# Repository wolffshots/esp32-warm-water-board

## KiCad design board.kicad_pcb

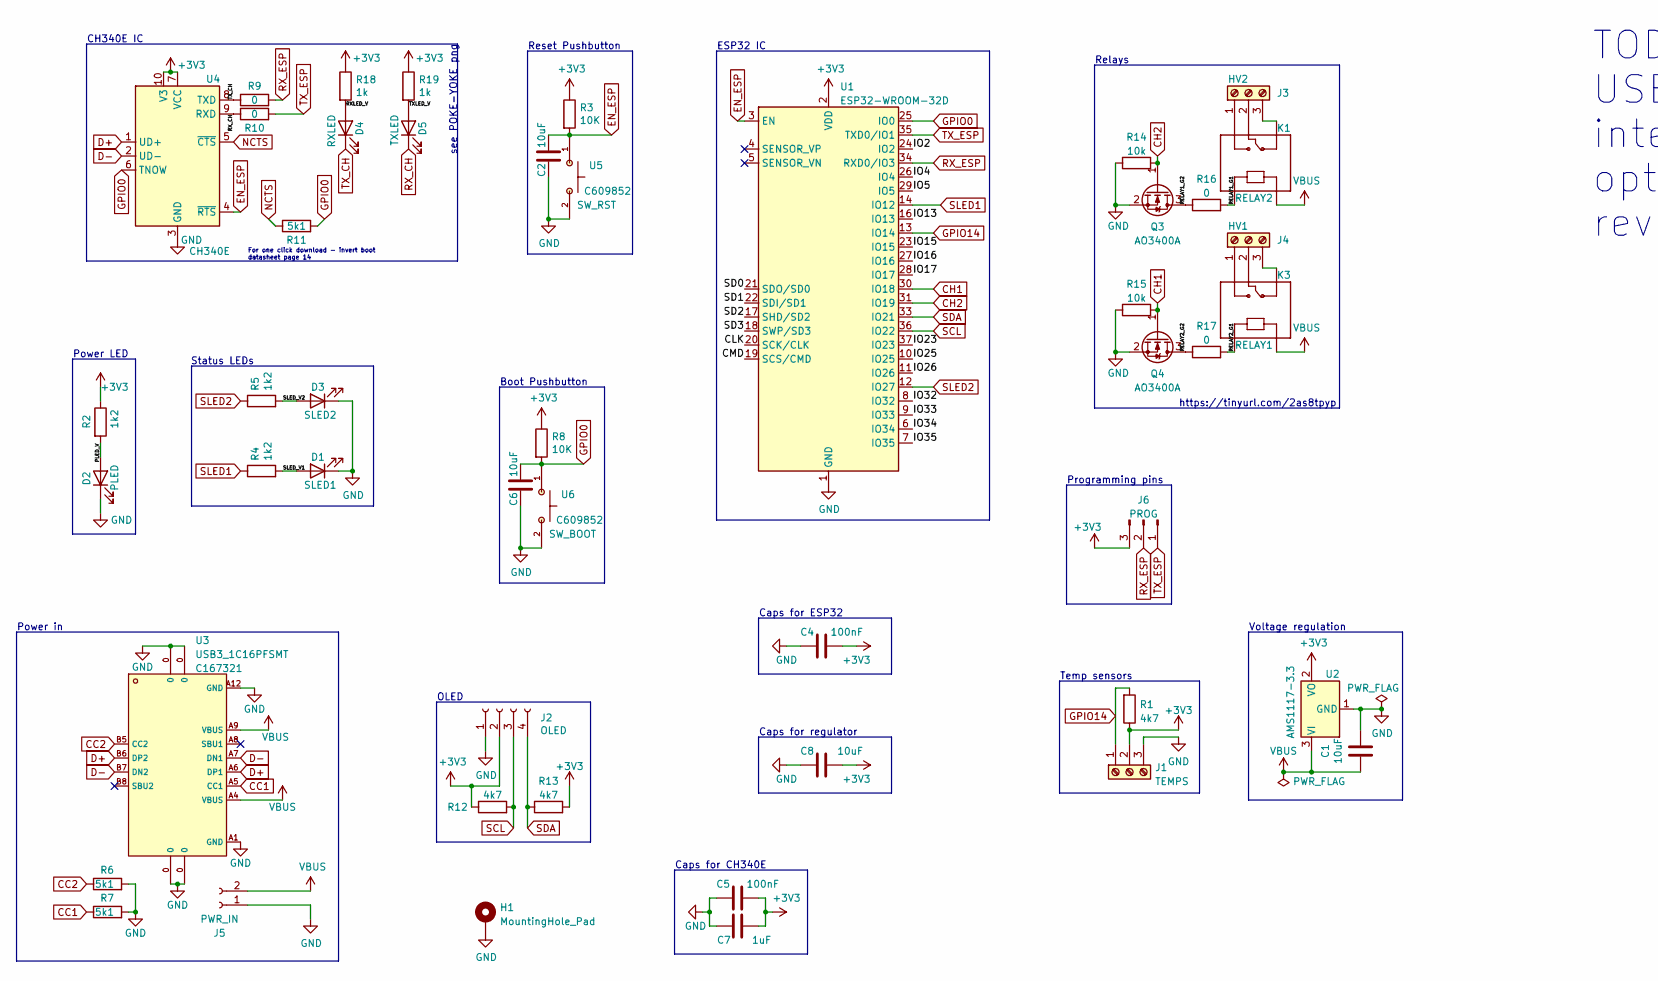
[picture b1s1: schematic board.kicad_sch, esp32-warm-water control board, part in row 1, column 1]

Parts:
C1, C2, C6: 10uF; C_0402_1005Metric; Part No C15850; LCSC C15850
C4, C5: 100nF; C_0402_1005Metric; Part No C49678; LCSC C49678
C7: 1uF; C_0402_1005Metric; Part No C15850; LCSC C15850
C8: 10uF; C_0402_1005Metric; Part No C49678; LCSC C49678
D1: SLED1; LED_0603_1608Metric; Part No C2286; LCSC C2286
D2: PLED; LED_0603_1608Metric; Part No C2286; LCSC C2286
D3: SLED2; LED_0603_1608Metric; Part No C2286; LCSC C2286
D4: RXLED; LED_0603_1608Metric; Part No C2286; LCSC C2286
D5: TXLED; LED_0603_1608Metric; Part No C2286; LCSC C2286
H1: MountingHole_Pad; MountingHole_2.2mm_M2_DIN965_Pad
J1: TEMPS; TerminalBlock_Phoenix_PT-1,5-3-5.0-H_1x03_P5.00mm_Horizontal
J2: OLED; PinSocket_1x04_P2.54mm_Vertical
J3: HV2; TerminalBlock_Phoenix_PT-1,5-3-5.0-H_1x03_P5.00mm_Horizontal
J4: HV1; TerminalBlock_Phoenix_PT-1,5-3-5.0-H_1x03_P5.00mm_Horizontal
J5: PWR_IN; PinHeader_2x01_P2.54mm_Vertical
J6: PROG; PinHeader_1x03_P2.54mm_Vertical
K1: RELAY2; RELAY_SRD-05VDC-SL-C
K3: RELAY1; RELAY_SRD-05VDC-SL-C
Q3, Q4: AO3400A; SOT-23
R1: 4k7; R_0402_1005Metric; Part No C17673; LCSC C17673
R2, R4, R5: 1k2; R_0402_1005Metric; Part No C17630; LCSC C17630
R3, R8: 10K; R_0402_1005Metric; Part No C17414; LCSC C17414
R6, R7, R11: 5k1; R_0402_1005Metric
R9, R10, R16, R17: 0; R_0402_1005Metric
R12, R13: 4k7; R_0402_1005Metric
R14, R15: 10k; R_0402_1005Metric
R18, R19: 1k; R_0402_1005Metric; Part No C17630; LCSC C17630
U1: ESP32-WROOM-32D; ESP32-WROOM-32
U2: AMS1117-3.3; SOT-223-3_TabPin2; Part No C6186; LCSC C6186
U3: USB3_1C16PFSMT; USB-C-SMD_TYPE-C-USB-17; LCSC C167321
U4: CH340E; MSOP-10_3x3mm_P0.5mm
U5: SW_RST; SW-SMD_L6.0-W3.5-LS8.0; LCSC C609852
U6: SW_BOOT; SW-SMD_L6.0-W3.5-LS8.0; LCSC C609852

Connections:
+3V3: C4.2, C5.2, C7.1, C8.2, J1.2, J2.2, J6.3, R1.1, R2.1, R3.1, R8.1, R12.1, R13.2, R18.1, R19.1, U1.2 (VDD), U2.2 (VO), U4.7 (VCC), U4.10 (V3)
/CLK: U1.20 (SCK/CLK)
/CMD: U1.19 (SCS/CMD)
/IO2: U1.24 (IO2)
/IO4: U1.26 (IO4)
/IO5: U1.29 (IO5)
/IO13: U1.16 (IO13)
/IO15: U1.23 (IO15)
/IO16: U1.27 (IO16)
/IO17: U1.28 (IO17)
/IO23: U1.37 (IO23)
/IO25: U1.10 (IO25)
/IO26: U1.11 (IO26)
/IO32: U1.8 (IO32)
/IO33: U1.9 (IO33)
/IO34: U1.6 (IO34)
/IO35: U1.7 (IO35)
/PLED_V: D2.2 (A), R2.2
/RELAY1_G1: K1.A1, R16.2
/RELAY1_G2: Q3.3 (D), R16.1
/RELAY2_G1: K3.A1, R17.2
/RELAY2_G2: Q4.3 (D), R17.1
/RXLED_V: D4.2 (A), R18.2
/SD0: U1.21 (SDO/SD0)
/SD1: U1.22 (SDI/SD1)
/SD2: U1.17 (SHD/SD2)
/SD3: U1.18 (SWP/SD3)
/SLED_V1: D1.2 (A), R4.2
/SLED_V2: D3.2 (A), R5.2
/TXLED_V: D5.2 (A), R19.2
CC1: R7.1, U3.A5 (CC1)
CC2: R6.1, U3.B5 (CC2)
CH1: Q4.1 (G), R15.2, U1.30 (IO18)
CH2: Q3.1 (G), R14.2, U1.31 (IO19)
D+: U3.A6 (DP1), U3.B6 (DP2), U4.1 (UD+)
D-: U3.A7 (DN1), U3.B7 (DN2), U4.2 (UD-)
EN_ESP: C2.2, R3.2, U1.3 (EN), U4.4 (~RTS), U5.1
GND: C1.1, C2.1, C4.1, C5.1, C6.1, C7.2, C8.1, D1.1 (K), D2.1 (K), D3.1 (K), H1.1, J1.3, J2.1, J5.1, Q3.2 (S), Q4.2 (S), R6.2, R7.2, R14.1, R15.1, U1.1 (GND), U1.15 (GND), U1.38 (GND), U1.39 (GND), U2.1 (GND), U3.0, U3.A1 (GND), U3.A12 (GND), U4.3 (GND), U5.2, U6.2
GPIO0: C6.2, R8.2, R11.2, U1.25 (IO0), U4.6 (TNOW), U6.1
GPIO14: J1.1, R1.2, U1.13 (IO14)
NCTS: R11.1, U4.5 (~CTS)
unnamed: J3.1, K1.NO
unnamed: J3.2, K1.COM
unnamed: J3.3, K1.NC
unnamed: J4.1, K3.NO
unnamed: J4.2, K3.COM
unnamed: J4.3, K3.NC
RX_CH: D5.1 (K), R10.1, U4.9 (RXD)
RX_ESP: J6.2, R9.2, U1.34 (RXD0/IO3)
SCL: J2.3, R12.2, U1.36 (IO22)
SDA: J2.4, R13.1, U1.33 (IO21)
SLED1: R4.1, U1.14 (IO12)
SLED2: R5.1, U1.12 (IO27)
TX_CH: D4.1 (K), R9.1, U4.8 (TXD)
TX_ESP: J6.1, R10.2, U1.35 (TXD0/IO1)
VBUS: C1.2, J5.2, K1.A2, K3.A2, U2.3 (VI), U3.A4 (VBUS), U3.A9 (VBUS)

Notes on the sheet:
TODO: USB footprint integrate relay (https://www.robotics.org.za/SRD-5VDC-SL-C) opto isolator EL3H7(B)(TA)-G review Schaltplan
Reset Pushbutton
CH340E IC
For one click download - invert boot datasheet page 14
Caps for ESP32
Voltage regulation
Power LED
Relays
Caps for regulator
Programming pins
https://tinyurl.com/2as8tpyp
ESP32 IC
OLED
Caps for CH340E
Status LEDs
Temp sensors
Power in
see POKE-YOKE png
Boot Pushbutton

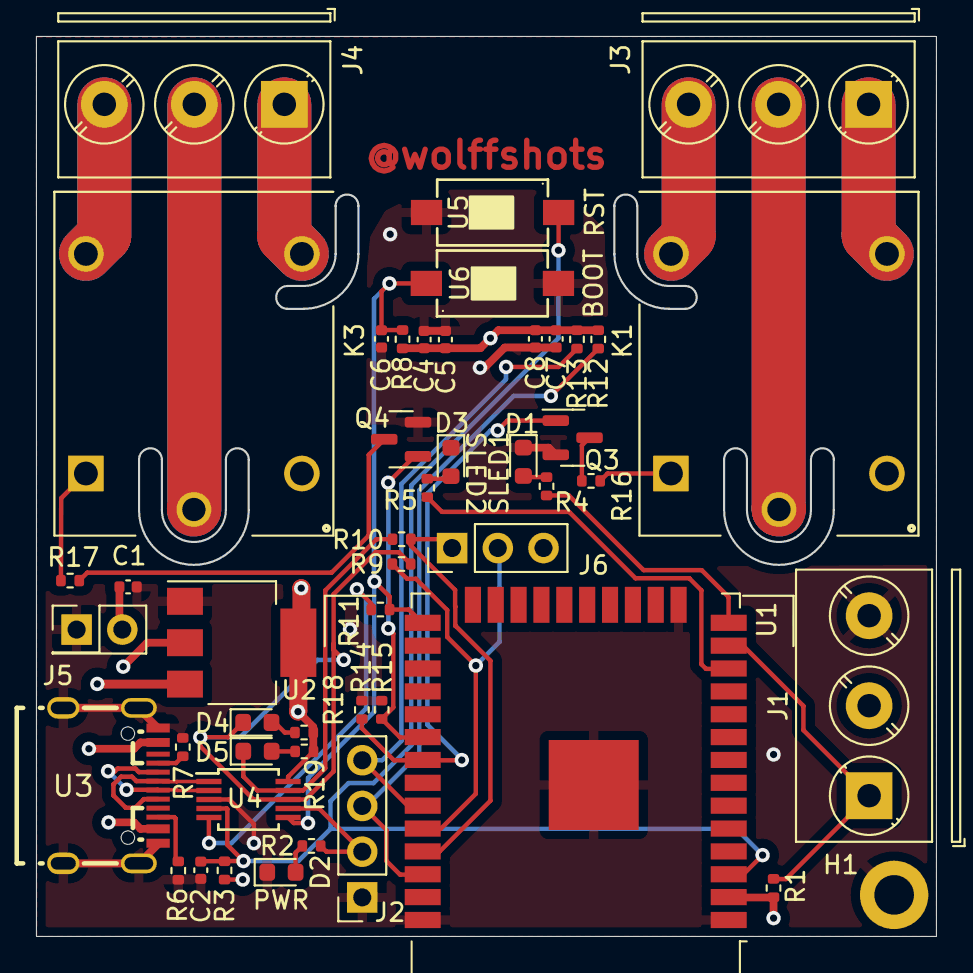
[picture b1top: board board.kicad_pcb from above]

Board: 4 copper layers, 49.9 x 49.9 mm, 48 parts (0 on the bottom side), 36 nets.

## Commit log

2021-06-19 added initial kicad files
2021-06-19 added esp chip
2021-06-19 removed extra level
2021-06-19 added labels
2021-07-06 initial fiddling with 3d board view
2021-07-08 added some redundant gitignore values from gitignore.io
2021-07-08 added programmer, usb and general design improvements to schematic and did some measuring for final board
2021-07-18 with programmer
2021-07-30 added step file to instpect in 3d viewers
2021-07-30 initial finished board pre-fab
2021-08-06 straightened inset line and edited page infos
2021-08-06 sourced components
2021-08-06 added gerber files and changed to 8mb esp
2022-05-29 feat: added usb connector and cp2104 and started redesign in kicad 6
2022-06-02 feat: added relays and reworked programming
2022-06-02 feat: added relative pathing for relay libs
2022-06-03 feat: added usb-c connector and switched to ch340e
2022-06-04 feat: redesigned board for 5x5
2022-06-04 feat: initial routing
2022-06-06 feat: routed with planes and no warnings or errors
2022-06-13 chore: reorganised to respect keepout and corners
2022-07-29 chore: switched esp footprint
